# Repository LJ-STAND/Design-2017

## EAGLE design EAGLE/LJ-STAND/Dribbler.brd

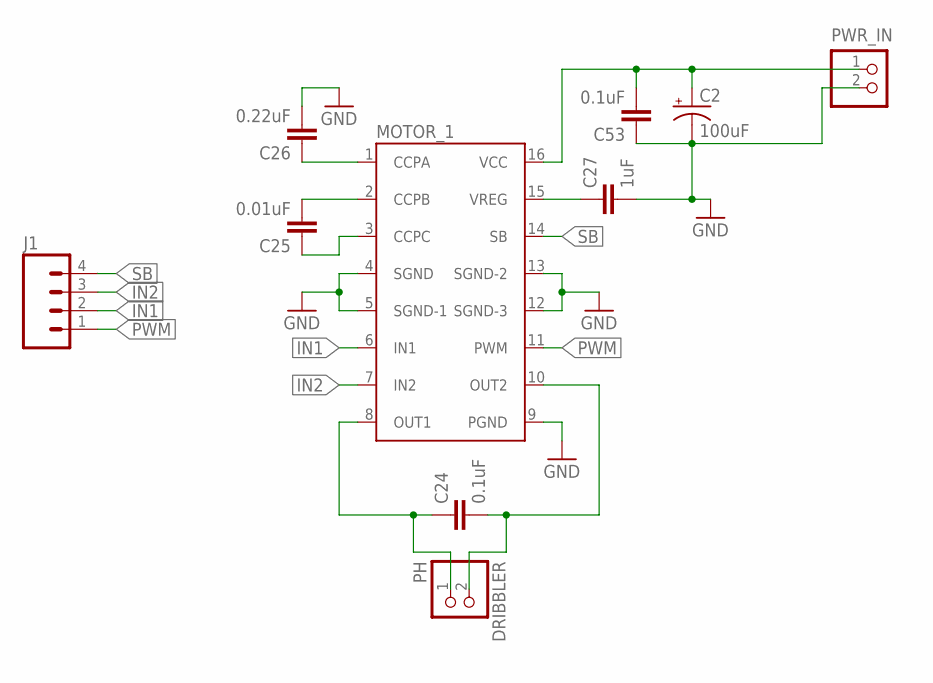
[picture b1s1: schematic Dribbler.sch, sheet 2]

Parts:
C2: 100uF; CPOL-RADIAL-100UF-25V
C24, C53: 0.1uF; 0603-CAP
C25: 0.01uF; 0603-CAP
C26: 0.22uF; 0603-CAP
C27: 1uF; 0603-CAP
DRIBBLER: PH; JST-PH-2-THM
J1: M04PTH; 1X04
MOTOR_1: TB6549PG
PWR_IN: B2P-VH

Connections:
GND: C2.2 (-), C26.2, C27.2, C53.1, MOTOR_1.4 (SGND), MOTOR_1.5 (SGND-1), MOTOR_1.9 (PGND), MOTOR_1.12 (SGND-3), MOTOR_1.13 (SGND-2), PWR_IN.2
IN1: J1.2, MOTOR_1.6 (IN1)
IN2: J1.3, MOTOR_1.7 (IN2)
MOTOR_PWR: C2.1 (+), C53.2, MOTOR_1.16 (VCC), PWR_IN.1
unnamed: C24.1, DRIBBLER.1 (2), MOTOR_1.8 (OUT1)
unnamed: C24.2, DRIBBLER.2 (1), MOTOR_1.10 (OUT2)
unnamed: C25.2, MOTOR_1.2 (CCPB)
unnamed: C25.1, MOTOR_1.3 (CCPC)
unnamed: C26.1, MOTOR_1.1 (CCPA)
unnamed: C27.1, MOTOR_1.15 (VREG)
PWM: J1.1, MOTOR_1.11 (PWM)
SB: J1.4, MOTOR_1.14 (SB)

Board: 2 copper layers, 10 parts (6 on the bottom side), 12 nets, no tracks yet.

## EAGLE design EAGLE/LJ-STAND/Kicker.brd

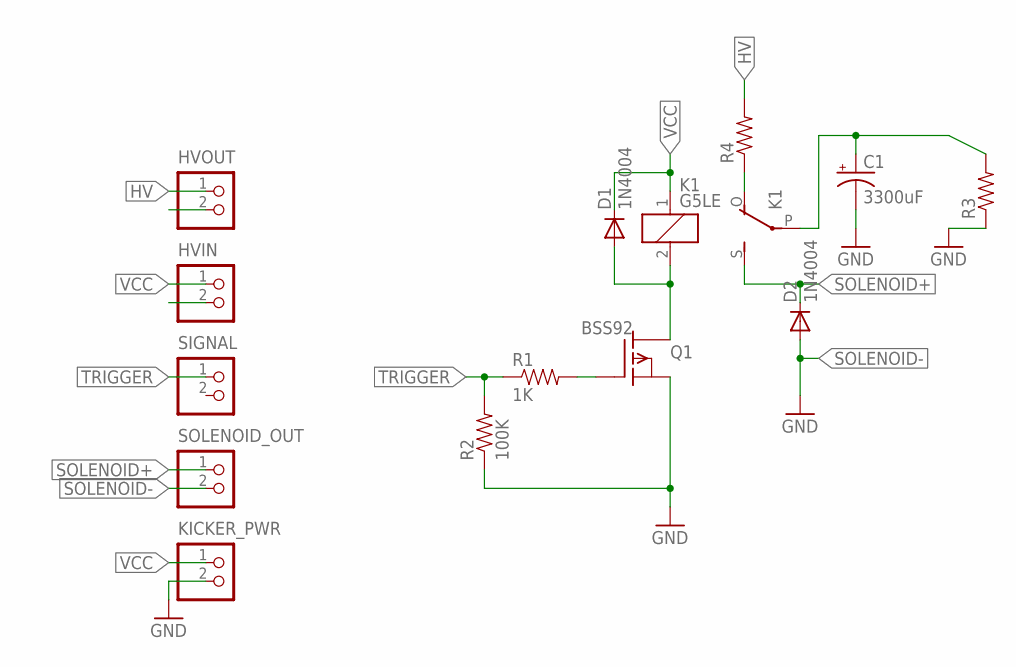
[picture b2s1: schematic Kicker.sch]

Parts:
C1: 3300uF; EB22,5D
D1, D2: 1N4004; DO41-10
HVIN: B2P-VH
HVOUT: B2P-VH
K1: G5LE
KICKER_PWR: B2P-VH
Q1: BSS92; TO92
R1: 1K; 0603-RES
R2: 100K; 0805
R3, R4: RESISTORPTH-2W; AXIAL-0.8
SIGNAL: B2B-PH-K-S
SOLENOID_OUT: B2P-VH

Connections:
GND: C1.-, KICKER_PWR.2, Q1.3 (S), R2.1, R3.P$1 (1)
HV: HVOUT.1, R4.P$2 (2)
unnamed: K1.O, R4.P$1 (1)
unnamed: Q1.1 (G), R1.2
unnamed: D1.A, K1.2, Q1.2 (D)
unnamed: C1.+, K1.P, R3.P$2 (2)
SOLENOID+: D2.C, K1.S, SOLENOID_OUT.1
SOLENOID-: D2.A, SOLENOID_OUT.2
TRIGGER: R1.1, R2.2, SIGNAL.1
VCC: D1.C, HVIN.1, K1.1, KICKER_PWR.1

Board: 2 copper layers, 14 parts (0 on the bottom side), 10 nets, no tracks yet.

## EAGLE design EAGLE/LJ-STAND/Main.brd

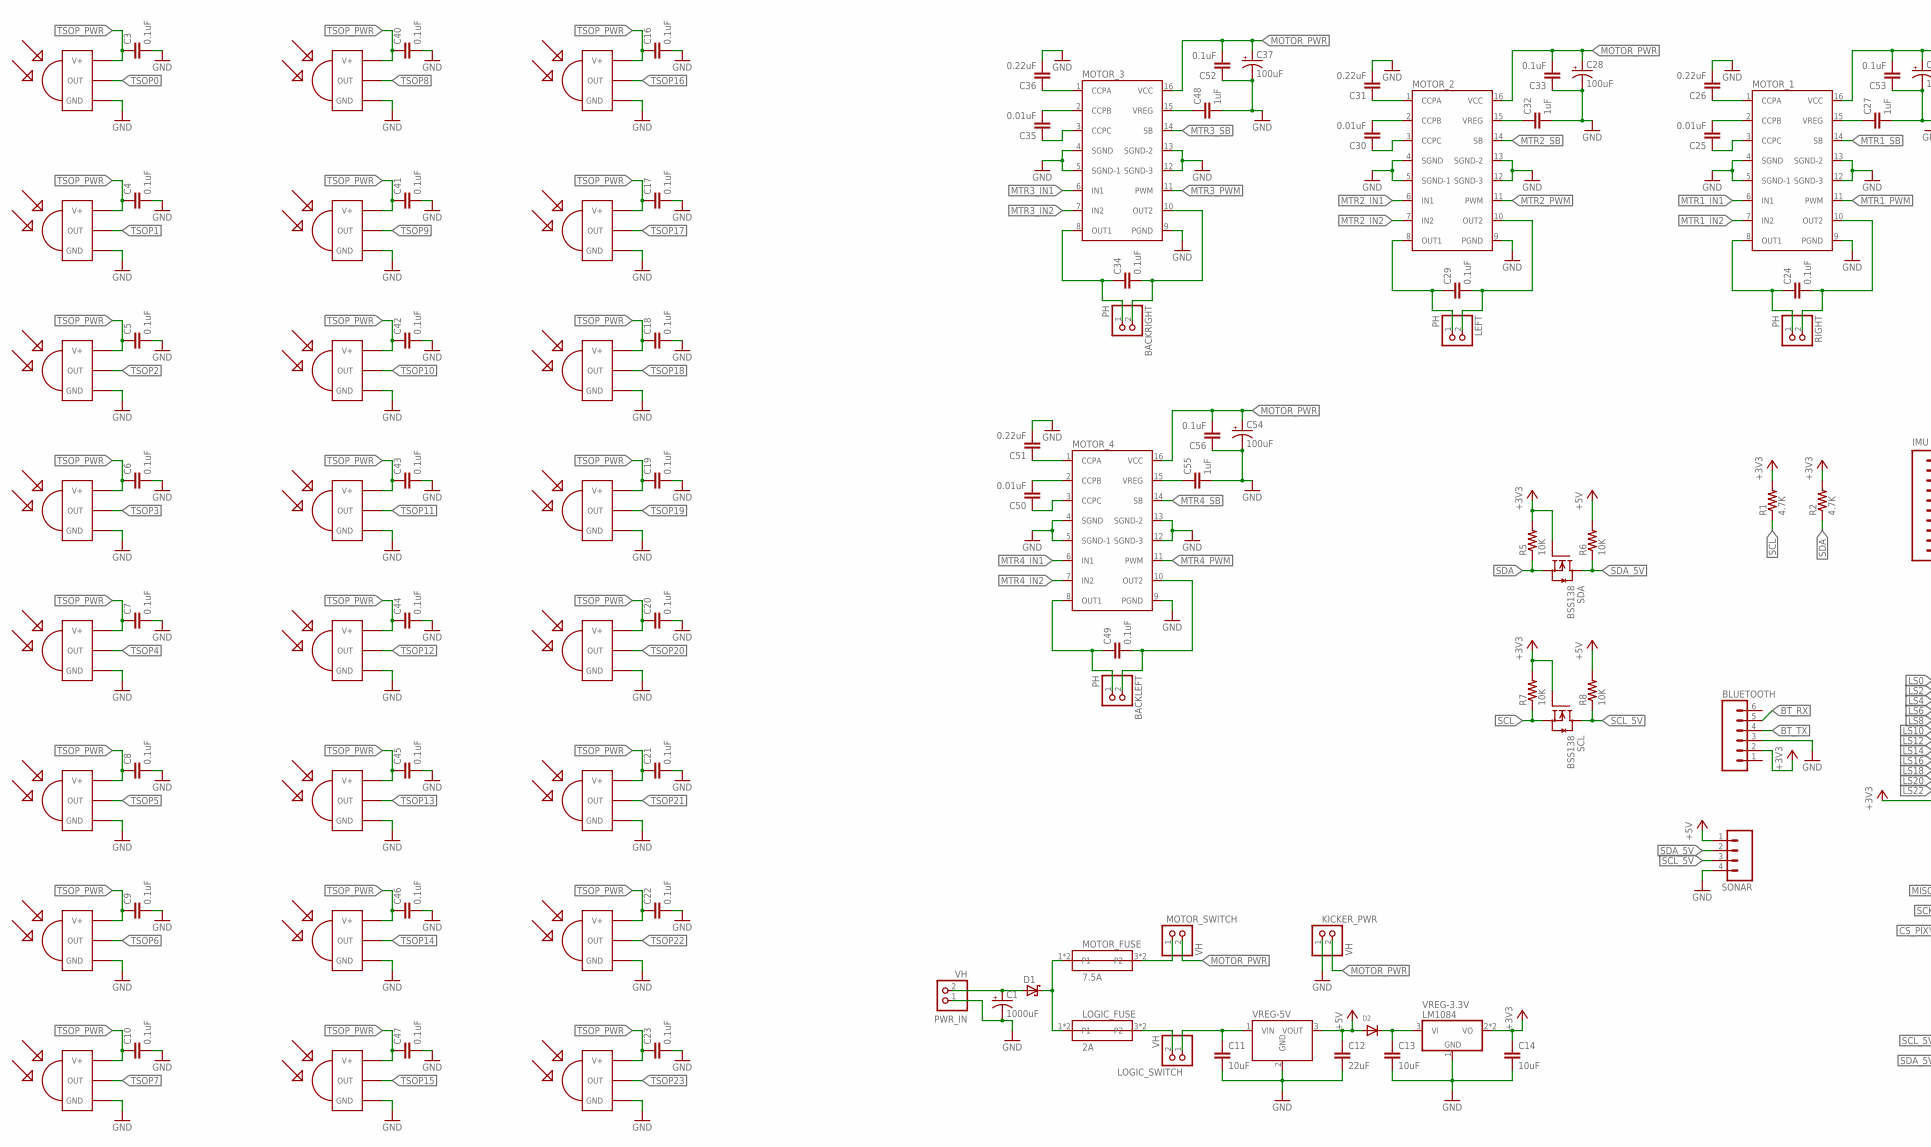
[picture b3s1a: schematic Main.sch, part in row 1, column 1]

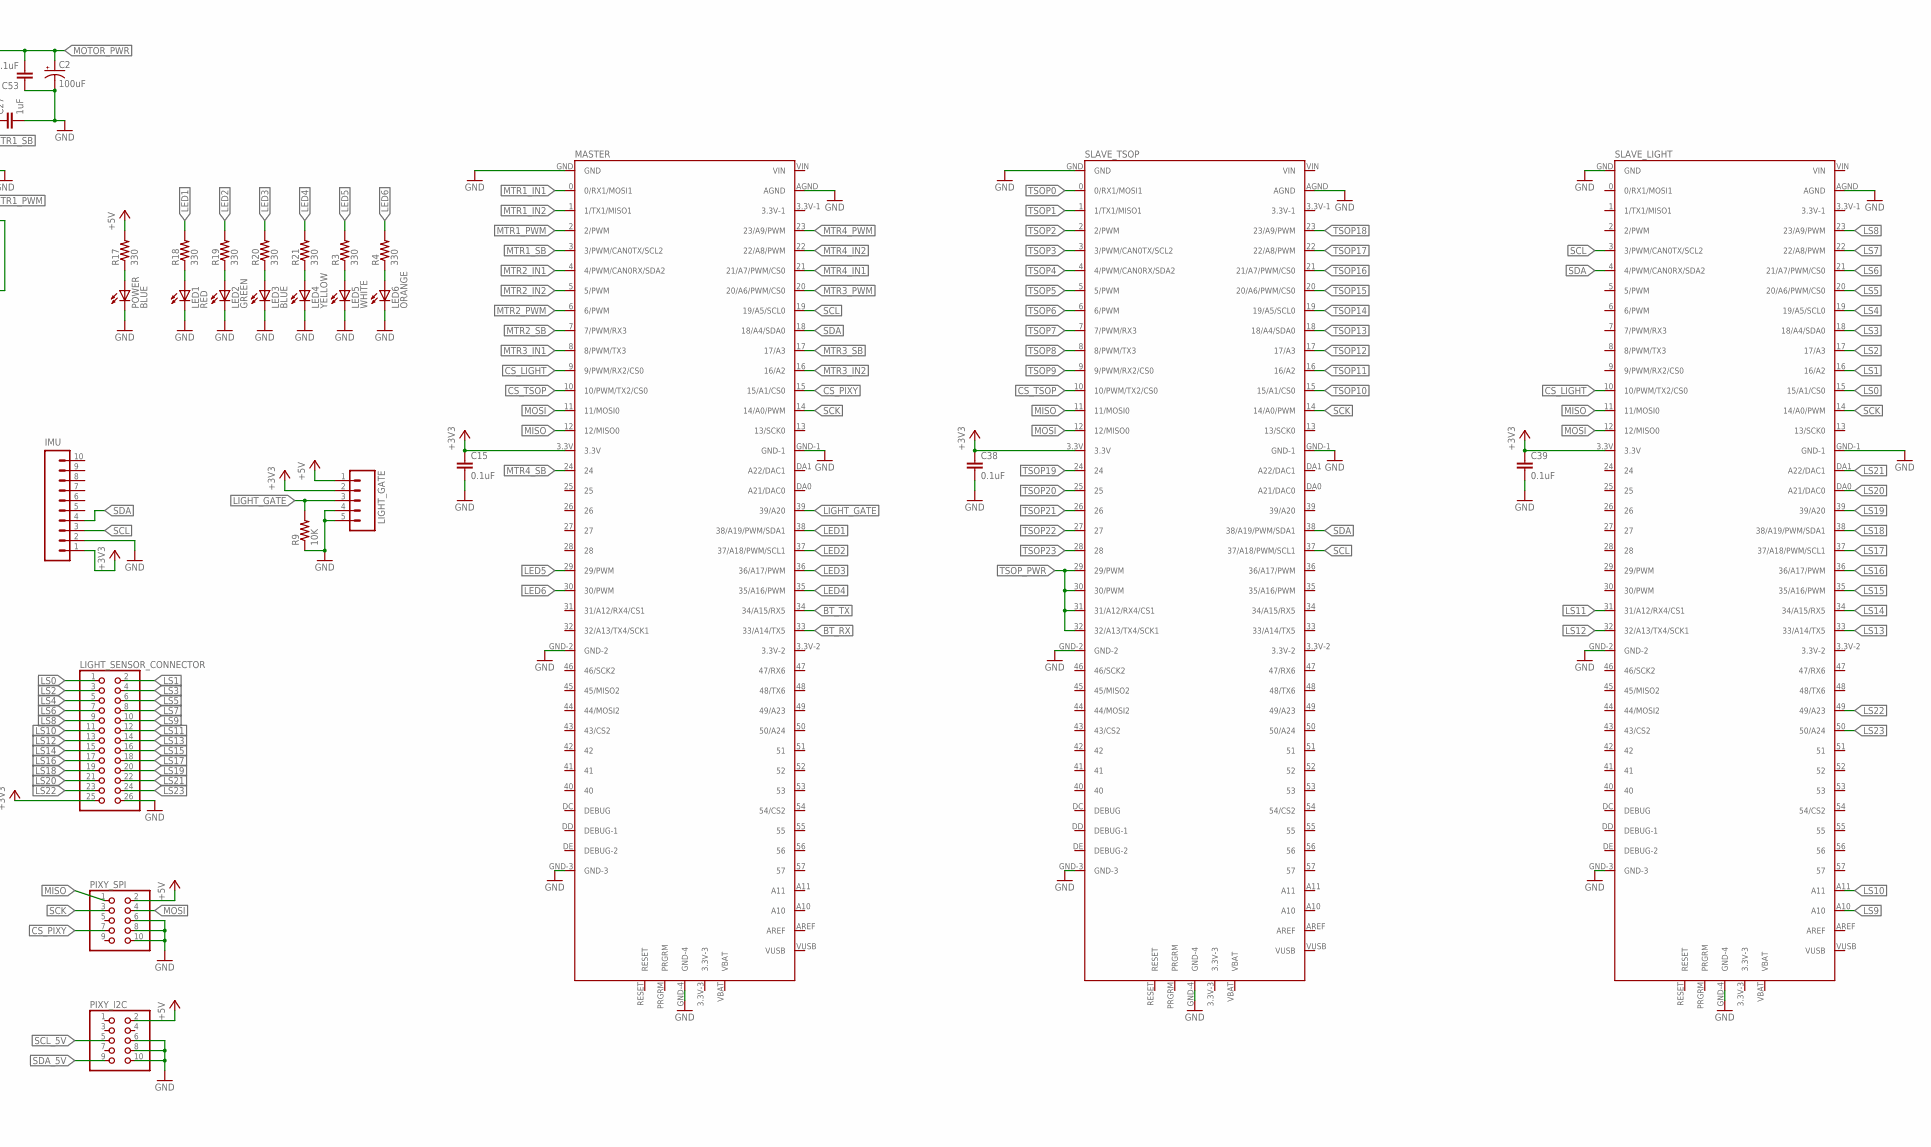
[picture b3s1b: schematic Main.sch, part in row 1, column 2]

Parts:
0, 1, 2, 3, 4, 5, 6, 7, 8, 9, 10, 11, 12, 13, 14, 15, 16, 17, 18, 19, 20, 21, 22, 23: TSOP1737; TSOP17XX
BACKLEFT: PH; JST-PH-2-THM
BACKRIGHT: PH; JST-PH-2-THM
BLUETOOTH: M06SILK_FEMALE_PTH; 1X06
C1: 1000uF; CPOL-RADIAL-1000UF-25V
C2, C28, C37, C54: 100uF; CPOL-RADIAL-100UF-25V
C3, C4, C5, C6, C7, C8, C9, C10, C15, C16, C17, C18, C19, C20, C21, C22, C23, C24, C29, C33, C34, C38, C39, C40, C41, C42, C43, C44, C45, C46, C47, C49, C52, C53, C56: 0.1uF; 0603-CAP
C11, C13, C14: 10uF; 0805
C12: 22uF; 0805
C25, C30, C35, C50: 0.01uF; 0603-CAP
C26, C31, C36, C51: 0.22uF; 0603-CAP
C27, C32, C48, C55: 1uF; 0603-CAP
D1: SCHOTTKY-DIODEP6T15; P6T15
D2: DIODE_SOD-123FL; SOD-123FL
IMU: M10SILK_FEMALE_PTH; 1X10
KICKER_PWR: VH; B2P-VH
LED1: RED; CHIPLED_0603
LED2: GREEN; CHIPLED_0603
LED3: BLUE; CHIPLED_0603
LED4: YELLOW; CHIPLED_0603
LED5: WHITE; CHIPLED_0603
LED6: ORANGE; CHIPLED_0603
LEFT: PH; JST-PH-2-THM
LIGHT_GATE: M05PTH; 1X05
LIGHT_SENSOR_CONNECTOR: PINHD-2X13SMT; 2X13_SMT
LOGIC_FUSE: 2A; 3568-FUSEHOLDER
LOGIC_SWITCH: VH; B2P-VH
MASTER: TEENSY-3.5
MOTOR_1, MOTOR_2, MOTOR_3, MOTOR_4: TB6549PG
MOTOR_FUSE: 7.5A; 3568-FUSEHOLDER
MOTOR_SWITCH: VH; B2P-VH
PIXY_I2C: PINHD-2X5SMT; 2X05_SMT
PIXY_SPI: PINHD-2X5SMT; 2X05_SMT
POWER: BLUE; CHIPLED_0603
PWR_IN: VH; B2P-VH
R1, R2: 4.7K; 0603-RES
R3, R4, R17, R18, R19, R20, R21: 330; 0603-RES
R5, R6, R7, R8, R9: 10K; 0603-RES
RIGHT: PH; JST-PH-2-THM
SCL: BSS138; SOT23
SDA: BSS138; SOT23
SLAVE_LIGHT: TEENSY-3.5
SLAVE_TSOP: TEENSY-3.5
SONAR: M04PTH; 1X04
VREG-3.3V: LM1084; TO263-3
VREG-5V: V78-2000

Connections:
+3V3: BLUETOOTH.2, C14.1, C15.1, C38.1, C39.1, IMU.1, LIGHT_GATE.2, LIGHT_SENSOR_CONNECTOR.25, MASTER.3.3V, R1.2, R2.2, R5.2, R7.2, SCL.1 (G), SDA.1 (G), SLAVE_LIGHT.3.3V, SLAVE_TSOP.3.3V, VREG-3.3V.2 (VO), VREG-3.3V.TAB (VO)
+5V: C12.1, D2.A, LIGHT_GATE.1, PIXY_I2C.2, PIXY_SPI.2, R6.2, R8.2, R17.2, SONAR.1, VREG-5V.3 (VOUT)
BT_RX: BLUETOOTH.5, MASTER.33 (33/A14/TX5)
BT_TX: BLUETOOTH.4, MASTER.34 (34/A15/RX5)
CS_LIGHT: MASTER.9 (9/PWM/RX2/CS0), SLAVE_LIGHT.10 (10/PWM/TX2/CS0)
CS_PIXY: MASTER.15 (15/A1/CS0), PIXY_SPI.7
CS_TSOP: MASTER.10 (10/PWM/TX2/CS0), SLAVE_TSOP.10 (10/PWM/TX2/CS0)
GND: 0.GND, 1.GND, 2.GND, 3.GND, 4.GND, 5.GND, 6.GND, 7.GND, 8.GND, 9.GND, 10.GND, 11.GND, 12.GND, 13.GND, 14.GND, 15.GND, 16.GND, 17.GND, 18.GND, 19.GND, 20.GND, 21.GND, 22.GND, 23.GND, BLUETOOTH.3, C1.-, C2.2 (-), C3.2, C4.2, C5.2, C6.2, C7.2, C8.2, C9.2, C10.2, C11.2, C12.2, C13.2, C14.2, C15.2, C16.2, C17.2, C18.2, C19.2, C20.2, C21.2, C22.2, C23.2, C26.2, C27.2, C28.2 (-), C31.2, C32.2, C33.1, C36.2, C37.2 (-), C38.2, C39.2, C40.2, C41.2, C42.2, C43.2, C44.2, C45.2, C46.2, C47.2, C48.2, C51.2, C52.1, C53.1, C54.2 (-), C55.2, C56.1, IMU.2, KICKER_PWR.1, LED1.C, LED2.C, LED3.C, LED4.C, LED5.C, LED6.C, LIGHT_GATE.4, LIGHT_GATE.5, LIGHT_SENSOR_CONNECTOR.26, MASTER.AGND, MASTER.GND, MASTER.GND-1, MASTER.GND-2, MASTER.GND-3, MASTER.GND-4, MOTOR_1.4 (SGND), MOTOR_1.5 (SGND-1), MOTOR_1.9 (PGND), MOTOR_1.12 (SGND-3), MOTOR_1.13 (SGND-2), MOTOR_2.4 (SGND), MOTOR_2.5 (SGND-1), MOTOR_2.9 (PGND), MOTOR_2.12 (SGND-3), MOTOR_2.13 (SGND-2), MOTOR_3.4 (SGND), MOTOR_3.5 (SGND-1), MOTOR_3.9 (PGND), MOTOR_3.12 (SGND-3), MOTOR_3.13 (SGND-2), MOTOR_4.4 (SGND), MOTOR_4.5 (SGND-1), MOTOR_4.9 (PGND), MOTOR_4.12 (SGND-3), MOTOR_4.13 (SGND-2), PIXY_I2C.6, PIXY_I2C.8, PIXY_I2C.10, PIXY_SPI.6, PIXY_SPI.8, PIXY_SPI.10, POWER.C, PWR_IN.1, R9.1, SLAVE_LIGHT.AGND, SLAVE_LIGHT.GND, SLAVE_LIGHT.GND-1, SLAVE_LIGHT.GND-2, SLAVE_LIGHT.GND-3, SLAVE_LIGHT.GND-4, SLAVE_TSOP.AGND, SLAVE_TSOP.GND, SLAVE_TSOP.GND-1, SLAVE_TSOP.GND-2, SLAVE_TSOP.GND-3, SLAVE_TSOP.GND-4, SONAR.4, VREG-3.3V.1 (GND), VREG-5V.2 (GND)
LED1: MASTER.38 (38/A19/PWM/SDA1), R18.2
LED2: MASTER.37 (37/A18/PWM/SCL1), R19.2
LED3: MASTER.36 (36/A17/PWM), R20.2
LED4: MASTER.35 (35/A16/PWM), R21.2
LED5: MASTER.29 (29/PWM), R3.2
LED6: MASTER.30 (30/PWM), R4.2
LIGHT_GATE: LIGHT_GATE.3, MASTER.39 (39/A20), R9.2
LS0: LIGHT_SENSOR_CONNECTOR.1, SLAVE_LIGHT.15 (15/A1/CS0)
LS1: LIGHT_SENSOR_CONNECTOR.2, SLAVE_LIGHT.16 (16/A2)
LS2: LIGHT_SENSOR_CONNECTOR.3, SLAVE_LIGHT.17 (17/A3)
LS3: LIGHT_SENSOR_CONNECTOR.4, SLAVE_LIGHT.18 (18/A4/SDA0)
LS4: LIGHT_SENSOR_CONNECTOR.5, SLAVE_LIGHT.19 (19/A5/SCL0)
LS5: LIGHT_SENSOR_CONNECTOR.6, SLAVE_LIGHT.20 (20/A6/PWM/CS0)
LS6: LIGHT_SENSOR_CONNECTOR.7, SLAVE_LIGHT.21 (21/A7/PWM/CS0)
LS7: LIGHT_SENSOR_CONNECTOR.8, SLAVE_LIGHT.22 (22/A8/PWM)
LS8: LIGHT_SENSOR_CONNECTOR.9, SLAVE_LIGHT.23 (23/A9/PWM)
LS9: LIGHT_SENSOR_CONNECTOR.10, SLAVE_LIGHT.A10
LS10: LIGHT_SENSOR_CONNECTOR.11, SLAVE_LIGHT.A11
LS11: LIGHT_SENSOR_CONNECTOR.12, SLAVE_LIGHT.31 (31/A12/RX4/CS1)
LS12: LIGHT_SENSOR_CONNECTOR.13, SLAVE_LIGHT.32 (32/A13/TX4/SCK1)
LS13: LIGHT_SENSOR_CONNECTOR.14, SLAVE_LIGHT.33 (33/A14/TX5)
LS14: LIGHT_SENSOR_CONNECTOR.15, SLAVE_LIGHT.34 (34/A15/RX5)
LS15: LIGHT_SENSOR_CONNECTOR.16, SLAVE_LIGHT.35 (35/A16/PWM)
LS16: LIGHT_SENSOR_CONNECTOR.17, SLAVE_LIGHT.36 (36/A17/PWM)
LS17: LIGHT_SENSOR_CONNECTOR.18, SLAVE_LIGHT.37 (37/A18/PWM/SCL1)
LS18: LIGHT_SENSOR_CONNECTOR.19, SLAVE_LIGHT.38 (38/A19/PWM/SDA1)
LS19: LIGHT_SENSOR_CONNECTOR.20, SLAVE_LIGHT.39 (39/A20)
LS20: LIGHT_SENSOR_CONNECTOR.21, SLAVE_LIGHT.DA0 (A21/DAC0)
LS21: LIGHT_SENSOR_CONNECTOR.22, SLAVE_LIGHT.DA1 (A22/DAC1)
LS22: LIGHT_SENSOR_CONNECTOR.23, SLAVE_LIGHT.49 (49/A23)
LS23: LIGHT_SENSOR_CONNECTOR.24, SLAVE_LIGHT.50 (50/A24)
MISO: MASTER.12 (12/MISO0), PIXY_SPI.1, SLAVE_LIGHT.11 (11/MOSI0), SLAVE_TSOP.11 (11/MOSI0)
MOSI: MASTER.11 (11/MOSI0), PIXY_SPI.4, SLAVE_LIGHT.12 (12/MISO0), SLAVE_TSOP.12 (12/MISO0)
MOTOR_PWR: C2.1 (+), C28.1 (+), C33.2, C37.1 (+), C52.2, C53.2, C54.1 (+), C56.2, KICKER_PWR.2, MOTOR_1.16 (VCC), MOTOR_2.16 (VCC), MOTOR_3.16 (VCC), MOTOR_4.16 (VCC), MOTOR_SWITCH.2
MTR1_IN1: MASTER.0 (0/RX1/MOSI1), MOTOR_1.6 (IN1)
MTR1_IN2: MASTER.1 (1/TX1/MISO1), MOTOR_1.7 (IN2)
MTR1_PWM: MASTER.2 (2/PWM), MOTOR_1.11 (PWM)
MTR1_SB: MASTER.3 (3/PWM/CAN0TX/SCL2), MOTOR_1.14 (SB)
MTR2_IN1: MASTER.4 (4/PWM/CAN0RX/SDA2), MOTOR_2.6 (IN1)
MTR2_IN2: MASTER.5 (5/PWM), MOTOR_2.7 (IN2)
MTR2_PWM: MASTER.6 (6/PWM), MOTOR_2.11 (PWM)
MTR2_SB: MASTER.7 (7/PWM/RX3), MOTOR_2.14 (SB)
MTR3_IN1: MASTER.8 (8/PWM/TX3), MOTOR_3.6 (IN1)
MTR3_IN2: MASTER.16 (16/A2), MOTOR_3.7 (IN2)
MTR3_PWM: MASTER.20 (20/A6/PWM/CS0), MOTOR_3.11 (PWM)
MTR3_SB: MASTER.17 (17/A3), MOTOR_3.14 (SB)
MTR4_IN1: MASTER.21 (21/A7/PWM/CS0), MOTOR_4.6 (IN1)
MTR4_IN2: MASTER.22 (22/A8/PWM), MOTOR_4.7 (IN2)
MTR4_PWM: MASTER.23 (23/A9/PWM), MOTOR_4.11 (PWM)
MTR4_SB: MASTER.24, MOTOR_4.14 (SB)
unnamed: C29.1, LEFT.1 (2), MOTOR_2.8 (OUT1)
unnamed: C29.2, LEFT.2 (1), MOTOR_2.10 (OUT2)
unnamed: C30.2, MOTOR_2.2 (CCPB)
unnamed: C30.1, MOTOR_2.3 (CCPC)
unnamed: C24.1, MOTOR_1.8 (OUT1), RIGHT.1 (2)
unnamed: C31.1, MOTOR_2.1 (CCPA)
unnamed: C24.2, MOTOR_1.10 (OUT2), RIGHT.2 (1)
unnamed: C48.1, MOTOR_3.15 (VREG)
unnamed: LOGIC_FUSE.3 (P2), LOGIC_FUSE.4 (P2), LOGIC_SWITCH.2
unnamed: C25.2, MOTOR_1.2 (CCPB)
unnamed: C11.1, LOGIC_SWITCH.1, VREG-5V.1 (VIN)
unnamed: C25.1, MOTOR_1.3 (CCPC)
unnamed: C26.1, MOTOR_1.1 (CCPA)
unnamed: BACKRIGHT.1 (2), C34.1, MOTOR_3.8 (OUT1)
unnamed: C27.1, MOTOR_1.15 (VREG)
unnamed: BACKRIGHT.2 (1), C34.2, MOTOR_3.10 (OUT2)
unnamed: C35.2, MOTOR_3.2 (CCPB)
unnamed: C35.1, MOTOR_3.3 (CCPC)
unnamed: C36.1, MOTOR_3.1 (CCPA)
unnamed: C55.1, MOTOR_4.15 (VREG)
unnamed: MOTOR_FUSE.3 (P2), MOTOR_FUSE.4 (P2), MOTOR_SWITCH.1
unnamed: BACKLEFT.1 (2), C49.1, MOTOR_4.8 (OUT1)
unnamed: LED2.A, R19.1
unnamed: LED3.A, R20.1
unnamed: LED4.A, R21.1
unnamed: BACKLEFT.2 (1), C49.2, MOTOR_4.10 (OUT2)
unnamed: POWER.A, R17.1
unnamed: C50.2, MOTOR_4.2 (CCPB)
unnamed: LED1.A, R18.1
unnamed: C50.1, MOTOR_4.3 (CCPC)
unnamed: C51.1, MOTOR_4.1 (CCPA)
unnamed: C32.1, MOTOR_2.15 (VREG)
unnamed: LED5.A, R3.1
unnamed: LED6.A, R4.1
unnamed: C1.+, D1.A, PWR_IN.2
unnamed: C13.1, D2.C, VREG-3.3V.3 (VI)
PWR: D1.C, LOGIC_FUSE.1, LOGIC_FUSE.2 (P1), MOTOR_FUSE.1, MOTOR_FUSE.2 (P1)
SCK: MASTER.14 (14/A0/PWM), PIXY_SPI.3, SLAVE_LIGHT.14 (14/A0/PWM), SLAVE_TSOP.14 (14/A0/PWM)
SCL: IMU.3, MASTER.19 (19/A5/SCL0), R1.1, R7.1, SCL.2 (S), SLAVE_LIGHT.3 (3/PWM/CAN0TX/SCL2), SLAVE_TSOP.37 (37/A18/PWM/SCL1)
SCL_5V: PIXY_I2C.5, R8.1, SCL.3 (D), SONAR.3
SDA: IMU.4, MASTER.18 (18/A4/SDA0), R2.1, R5.1, SDA.2 (S), SLAVE_LIGHT.4 (4/PWM/CAN0RX/SDA2), SLAVE_TSOP.38 (38/A19/PWM/SDA1)
SDA_5V: PIXY_I2C.9, R6.1, SDA.3 (D), SONAR.2
TSOP0: 0.OUT, SLAVE_TSOP.0 (0/RX1/MOSI1)
TSOP1: 1.OUT, SLAVE_TSOP.1 (1/TX1/MISO1)
TSOP2: 2.OUT, SLAVE_TSOP.2 (2/PWM)
TSOP3: 3.OUT, SLAVE_TSOP.3 (3/PWM/CAN0TX/SCL2)
TSOP4: 4.OUT, SLAVE_TSOP.4 (4/PWM/CAN0RX/SDA2)
TSOP5: 5.OUT, SLAVE_TSOP.5 (5/PWM)
TSOP6: 6.OUT, SLAVE_TSOP.6 (6/PWM)
TSOP7: 7.OUT, SLAVE_TSOP.7 (7/PWM/RX3)
TSOP8: 8.OUT, SLAVE_TSOP.8 (8/PWM/TX3)
TSOP9: 9.OUT, SLAVE_TSOP.9 (9/PWM/RX2/CS0)
TSOP10: 10.OUT, SLAVE_TSOP.15 (15/A1/CS0)
TSOP11: 11.OUT, SLAVE_TSOP.16 (16/A2)
TSOP12: 12.OUT, SLAVE_TSOP.17 (17/A3)
TSOP13: 13.OUT, SLAVE_TSOP.18 (18/A4/SDA0)
TSOP14: 14.OUT, SLAVE_TSOP.19 (19/A5/SCL0)
TSOP15: 15.OUT, SLAVE_TSOP.20 (20/A6/PWM/CS0)
TSOP16: 16.OUT, SLAVE_TSOP.21 (21/A7/PWM/CS0)
TSOP17: 17.OUT, SLAVE_TSOP.22 (22/A8/PWM)
TSOP18: 18.OUT, SLAVE_TSOP.23 (23/A9/PWM)
TSOP19: 19.OUT, SLAVE_TSOP.24
TSOP20: 20.OUT, SLAVE_TSOP.25
TSOP21: 21.OUT, SLAVE_TSOP.26
TSOP22: 22.OUT, SLAVE_TSOP.27
TSOP23: 23.OUT, SLAVE_TSOP.28
TSOP_PWR: 0.V+, 1.V+, 2.V+, 3.V+, 4.V+, 5.V+, 6.V+, 7.V+, 8.V+, 9.V+, 10.V+, 11.V+, 12.V+, 13.V+, 14.V+, 15.V+, 16.V+, 17.V+, 18.V+, 19.V+, 20.V+, 21.V+, 22.V+, 23.V+, C3.1, C4.1, C5.1, C6.1, C7.1, C8.1, C9.1, C10.1, C16.1, C17.1, C18.1, C19.1, C20.1, C21.1, C22.1, C23.1, C40.1, C41.1, C42.1, C43.1, C44.1, C45.1, C46.1, C47.1, SLAVE_TSOP.29 (29/PWM), SLAVE_TSOP.30 (30/PWM), SLAVE_TSOP.31 (31/A12/RX4/CS1), SLAVE_TSOP.32 (32/A13/TX4/SCK1)

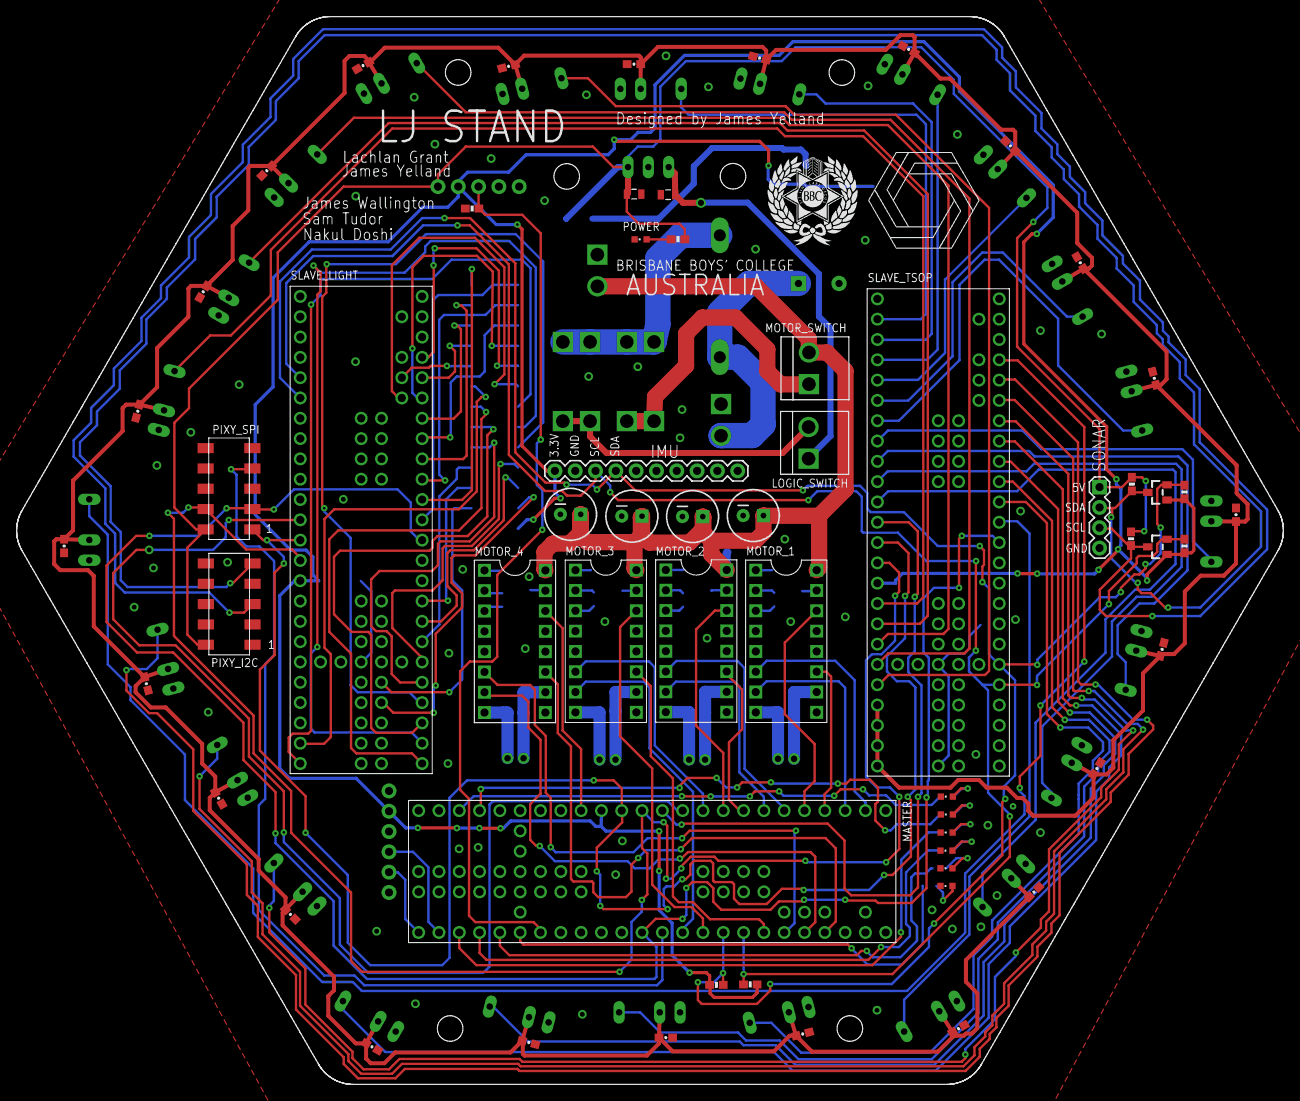
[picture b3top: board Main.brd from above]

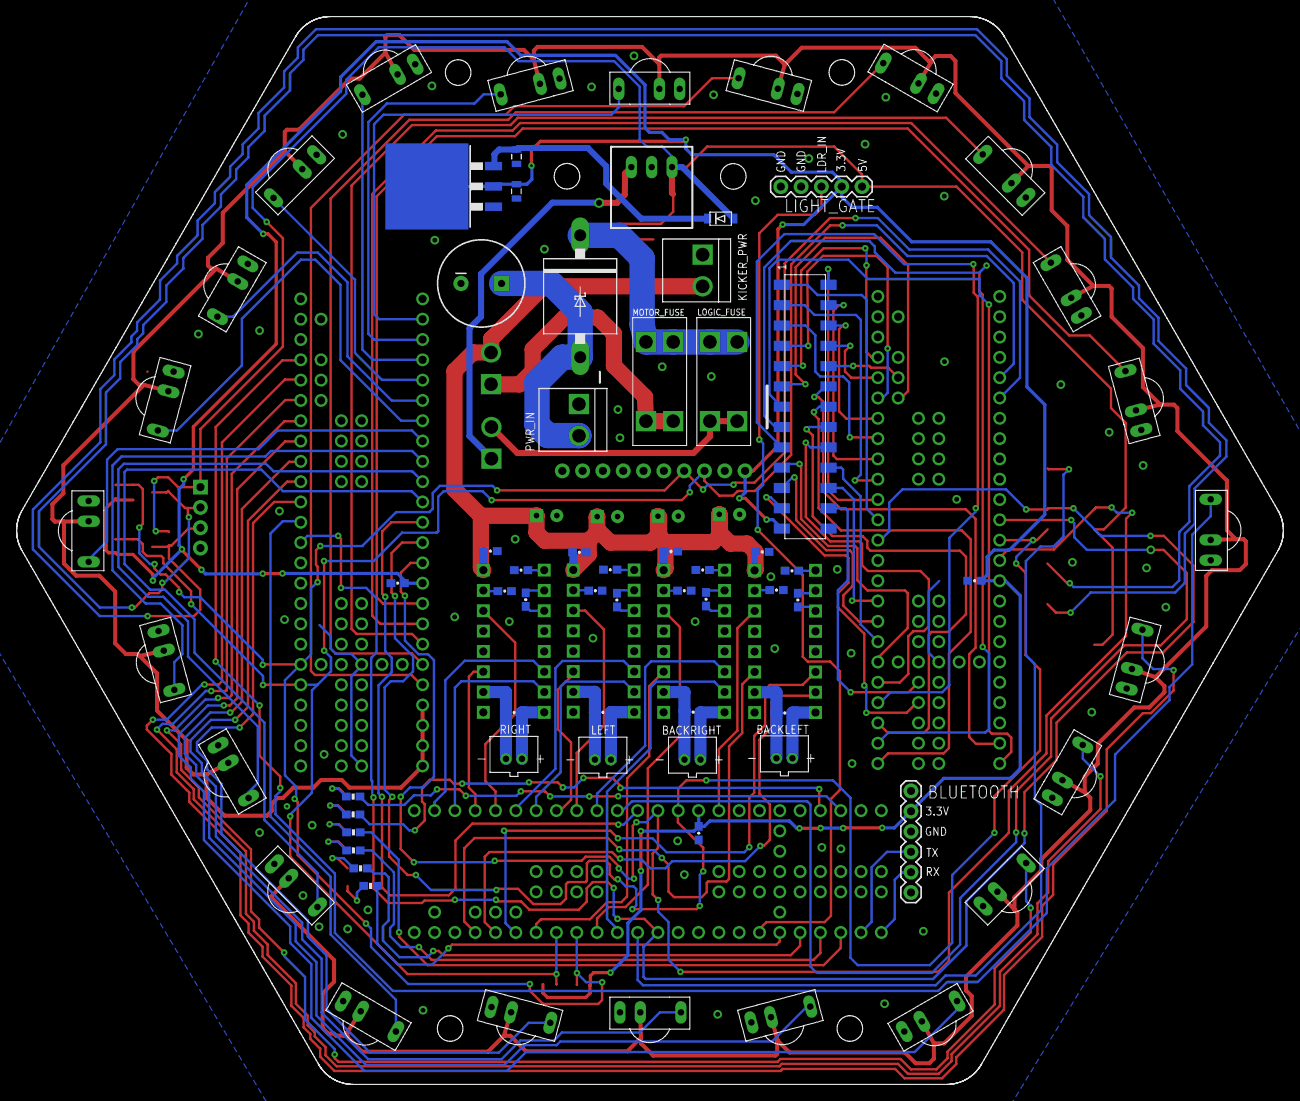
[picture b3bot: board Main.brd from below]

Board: 2 copper layers, 158.5 x 133.6 mm, 131 parts (71 on the bottom side), 125 nets.

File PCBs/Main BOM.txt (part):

Partlist exported from C:/Users/James Yelland/git/LJ-STAND/Design/EAGLE/LJ-STAND/Main.sch at 30/11/2016 5:48:50 PM

Qty Value      Device              Package                Parts                                                                                                                                                                  Description                                                                                    
` 1              DIODE_SOD-123FL     SOD-123FL              D2                                                                                                                                                                     Diode                                                                                          
` 1              M04PTH              1X04                   SONAR                                                                                                                                                                  Header 4                                                                                       
` 1              M05PTH              1X05                   LIGHT_GATE                                                                                                                                                             Header 5                                                                                       
` 1              M06SILK_FEMALE_PTH  1X06                   BLUETOOTH                                                                                                                                                              Header 6                                                                                       
` 1              M10SILK_FEMALE_PTH  1X10                   IMU                                                                                                                                                                    Header 10                                                                                      
` 1              PINHD-2X13SMT       2X13_SMT               LIGHT_SENSOR_CONNECTOR                                                                                                                                                 PIN HEADER                                                                                     
` 2              PINHD-2X5SMT        2X05_SMT               PIXY_I2C, PIXY_SPI                                                                                                                                                     PIN HEADER                                                                                     
` 1              SCHOTTKY-DIODEP6T15 P6T15                  D1                                                                                                                                                                     Schottky Diode                                                                                 
` 4   0.01uF     CAP0603-CAP         0603-CAP               C25, C30, C35, C50                                                                                                                                                     Capacitor                                                                                      
` 35  0.1uF      CAP0603-CAP         0603-CAP               C3, C4, C5, C6, C7, C8, C9, C10, C15, C16, C17, C18, C19, C20, C21, C22, C23, C24, C29, C33, C34, C38, C39, C40, C41, C42, C43, C44, C45, C46, C47, C49, C52, C53, C56 Capacitor                                                                                      
` 4   0.22uF     CAP0603-CAP         0603-CAP               C26, C31, C36, C51                                                                                                                                                     Capacitor                                                                                      
` 1   1000uF     CAP_POLPTH4         CPOL-RADIAL-1000UF-25V C1                                                                                                                                                                     Capacitor Polarized                                                                            
` 4   100uF      CAP_POLPTH1         CPOL-RADIAL-100UF-25V  C2, C28, C37, C54                                                                                                                                                      Capacitor Polarized                                                                            
` 5   10K        RESISTOR0603-RES    0603-RES               R5, R6, R7, R8, R9                                                                                                                                                     Resistor                                                                                       
` 3   10uF       CAP0805             0805                   C11, C13, C14                                                                                                                                                          Capacitor                                                                                      
` 4   1uF        CAP0603-CAP         0603-CAP               C27, C32, C48, C55                                                                                                                                                     Capacitor                                                                                      
` 1   22uF       CAP0805             0805                   C12                                                                                                                                                                    Capacitor                                                                                      
` 1   2A         3568-FUSEHOLDER     3568-FUSEHOLDER        LOGIC_FUSE                                                                                                                                                                                                                                                            
` 7   330        RESISTOR0603        0603-RES               R3, R4, R17, R18, R19, R20, R21                                                                                                                                        Resistor                                                                                       
` 2   4.7K       RESISTOR0603        0603-RES               R1, R2                                                                                                                                                                 Resistor                                                                                       
` 1   7.5A       3568-FUSEHOLDER     3568-FUSEHOLDER        MOTOR_FUSE                                                                                                                                                                                                                                                            
` 1   BLUE       LEDCHIPLED_0603     CHIPLED_0603           PWR                                                                                                                                                                    LED                                                                                            
` 2   BSS138     BSS138              SOT23                  SCL, SDA                                                                                                                                                               Fairchild Semiconductors BSS138 N-Channel Logic Level Enhancement Mode Field Effect Transistor 
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

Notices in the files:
parts and their libraries:
SparkFun-Capacitors: Licensing: Creative Commons ShareAlike 4.0 International - https://creativecommons.org/licenses/by-sa/4.0
m-pad-2.1: License : GNU General Public License version 2 (see bottom)
